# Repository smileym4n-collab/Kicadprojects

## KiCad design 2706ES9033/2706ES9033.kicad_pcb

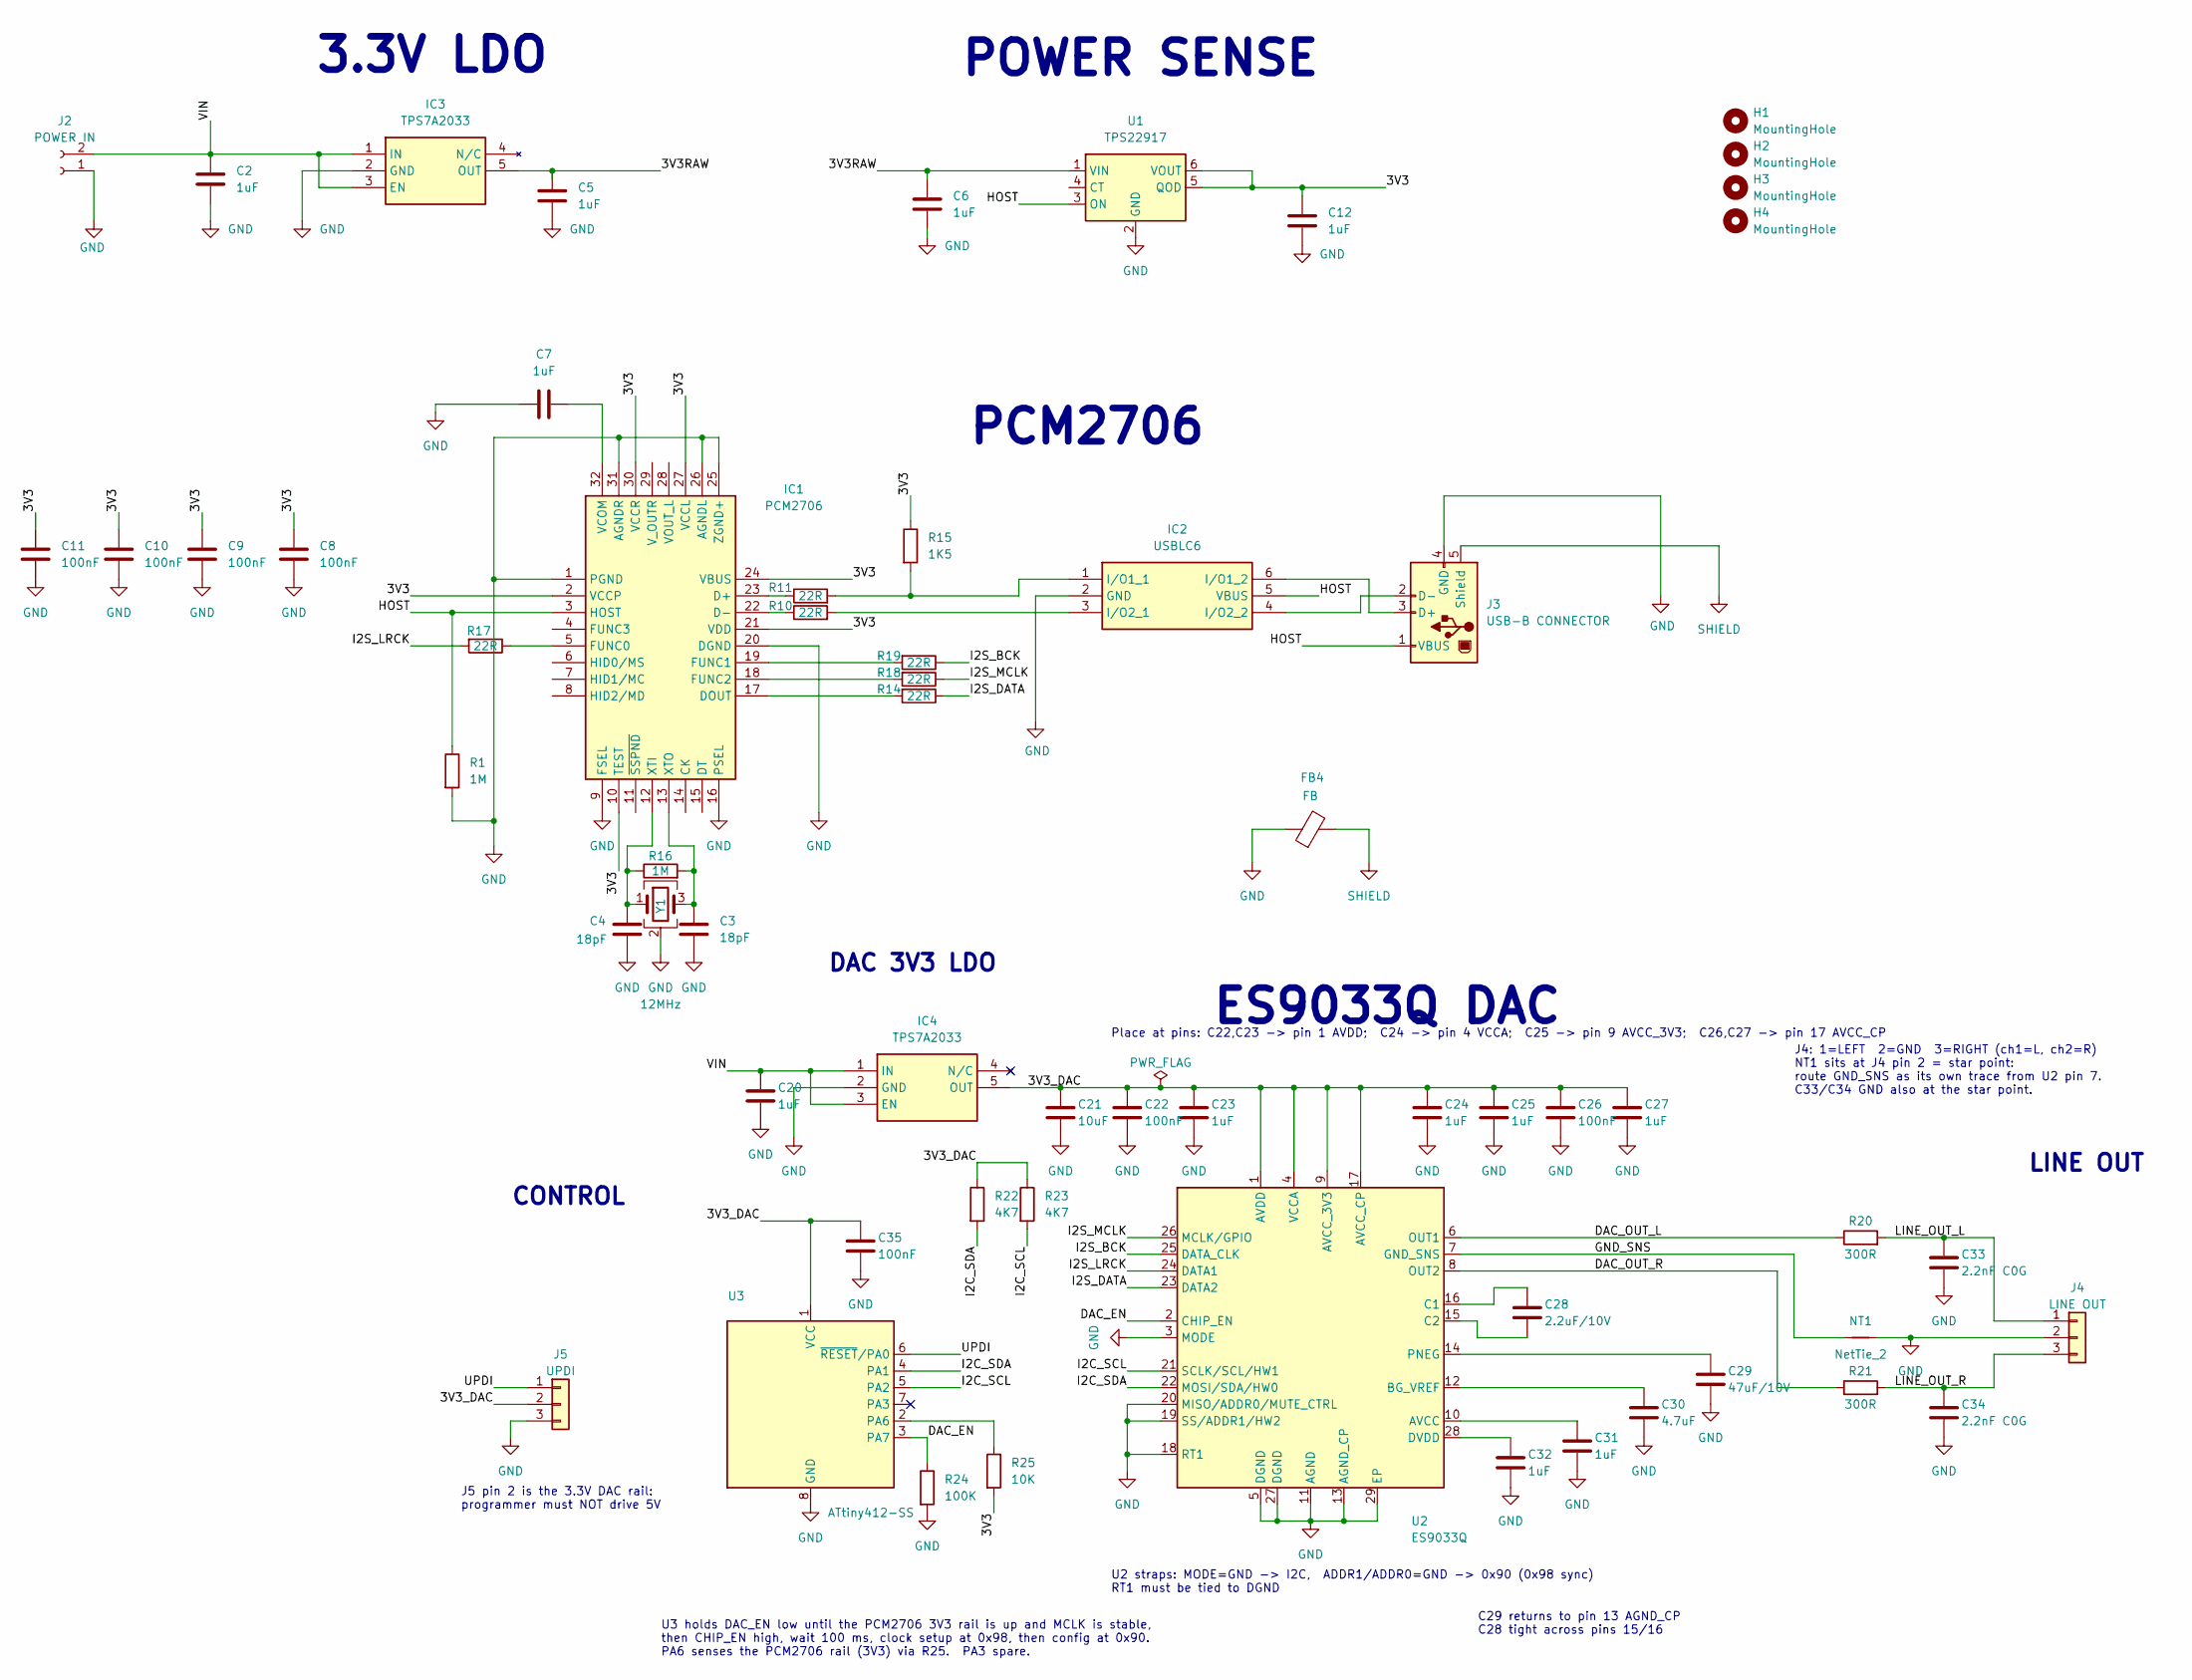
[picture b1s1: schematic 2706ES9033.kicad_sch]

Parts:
C2, C5, C6, C7, C12: 1uF; C_0805_2012Metric_Pad1.18x1.45mm_HandSolder
C3, C4: 18pF; C_0603_1608Metric_Pad1.08x0.95mm_HandSolder
C8, C9, C10, C11: 100nF; C_0603_1608Metric_Pad1.08x0.95mm_HandSolder
C20, C23, C24, C25, C27, C31, C32: 1uF; C_0805_2012Metric_Pad1.18x1.45mm_HandSolder; MPN C0805C105K3RACTU
C21: 10uF; C_1206_3216Metric_Pad1.33x1.80mm_HandSolder; MPN TMK316B7106KL-TD
C22, C26, C35: 100nF; C_0603_1608Metric_Pad1.08x0.95mm_HandSolder; MPN MC0603B104K500CT
C28: 2.2uF/10V; C_0805_2012Metric_Pad1.18x1.45mm_HandSolder; MPN CL21B225KPFNNNE
C29: 47uF/10V; C_1206_3216Metric_Pad1.33x1.80mm_HandSolder; MPN CL31A476MPHNNNE
C30: 4.7uF; C_0805_2012Metric_Pad1.18x1.45mm_HandSolder; MPN CL21A475KAQNNNE
C33, C34: 2.2nF C0G; C_0805_2012Metric_Pad1.18x1.45mm_HandSolder; MPN GCM2165C2A222FA16D
FB4: FB; L_1206_3216Metric_Pad1.42x1.75mm_HandSolder
H1, H2, H3, H4: MountingHole; MountingHole_3.2mm_M3
IC1: PCM2706; PCM2706C; Mouser Part Number 595-PCM2706CPJTR
IC2: USBLC6; SOT-23-6_Handsoldering; Mouser Part Number 511-USBLC6-2SC6
IC3: TPS7A2033; SOT95P280X145-5N; Mouser Part Number 595-TPS7A2033PDBVR
IC4: TPS7A2033; SOT95P280X145-5N; MPN TPS7A2033PDBVR
J2: POWER IN; JST_XH_B2B-XH-A_1x02_P2.50mm_Vertical
J3: USB-B CONNECTOR; USBC
J4: LINE OUT; Molex_KK-254_AE-6410-03A_1x03_P2.54mm_Vertical; MPN MC34631
J5: UPDI; Molex_KK-254_AE-6410-03A_1x03_P2.54mm_Vertical; MPN MC34631
NT1: NetTie_2; NetTie-2_SMD_Pad0.5mm
R1, R16: 1M; R_0603_1608Metric_Pad0.98x0.95mm_HandSolder
R10, R11, R14, R17, R18, R19: 22R; R_0603_1608Metric_Pad0.98x0.95mm_HandSolder
R15: 1K5; R_0603_1608Metric_Pad0.98x0.95mm_HandSolder
R20, R21: 300R; R_0805_2012Metric_Pad1.20x1.40mm_HandSolder; MPN ERA-6AEB301V
R22, R23: 4K7; R_0805_2012Metric_Pad1.20x1.40mm_HandSolder; MPN RMCF0805FT4K70
R24: 100K; R_0805_2012Metric_Pad1.20x1.40mm_HandSolder; MPN RK73B2ATTE104J
R25: 10K; R_0805_2012Metric_Pad1.20x1.40mm_HandSolder; MPN RK73B2ATTD103J
U1: TPS22917; SOT-23-6
U2: ES9033Q; ESS_QFN-28-1EP_5x5mm_P0.5mm_EP3.15x3.15mm; MPN ES9033Q
U3: ATtiny412-SS; SOIC-8_3.9x4.9mm_P1.27mm; MPN ATTINY412-SSN
Y1: 12MHz; Crystal_SMD_3225-4Pin_3.2x2.5mm; MPN 830108338809; Mouser Part Number 710-830108338809

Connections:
/3V3: C8.1, C9.1, C10.1, C11.1, C12.1, IC1.2 (VCCP), IC1.10 (TEST), IC1.21 (VDD), IC1.24 (VBUS), IC1.27 (VCCL), IC1.30 (VCCR), R15.1, R25.2, U1.5 (QOD), U1.6 (VOUT)
/3V3RAW: C5.1, C6.1, IC3.5 (OUT), U1.1 (VIN)
/3V3_DAC: C21.1, C22.1, C23.1, C24.1, C25.1, C26.1, C27.1, C35.1, IC4.5 (OUT), J5.2, R22.1, R23.1, U2.1 (AVDD), U2.4 (VCCA), U2.9 (AVCC_3V3), U2.17 (AVCC_CP), U3.1 (VCC)
/DAC_EN: R24.1, U2.2 (CHIP_EN), U3.3 (PA7)
/DAC_OUT_L: R20.1, U2.6 (OUT1)
/DAC_OUT_R: R21.1, U2.8 (OUT2)
/GND_SNS: NT1.1, U2.7 (GND_SNS)
/HOST: IC1.3 (HOST), IC2.5 (VBUS), J3.1 (VBUS), R1.1, U1.3 (ON)
/I2C_SCL: R23.2, U2.21 (SCLK/SCL/HW1), U3.5 (PA2)
/I2C_SDA: R22.2, U2.22 (MOSI/SDA/HW0), U3.4 (PA1)
/I2S_BCK: R19.1, U2.25 (DATA_CLK)
/I2S_DATA: R14.1, U2.23 (DATA2)
/I2S_LRCK: R17.2, U2.24 (DATA1)
/I2S_MCLK: R18.1, U2.26 (MCLK/GPIO)
/LINE_OUT_L: C33.1, J4.1, R20.2
/LINE_OUT_R: C34.1, J4.3, R21.2
/UPDI: J5.1, U3.6 (~RESET/PA0)
/VIN: C2.1, C20.1, IC3.1 (IN), IC3.3 (EN), IC4.1 (IN), IC4.3 (EN), J2.2
GND: C2.2, C3.2, C4.2, C5.2, C6.2, C7.1, C8.2, C9.2, C10.2, C11.2, C12.2, C20.2, C21.2, C22.2, C23.2, C24.2, C25.2, C26.2, C27.2, C29.2, C30.2, C31.2, C32.2, C33.2, C34.2, C35.2, FB4.1, IC1.1 (PGND), IC1.9 (FSEL), IC1.16 (PSEL), IC1.20 (DGND), IC1.25 (ZGND+), IC1.26 (AGNDL), IC1.31 (AGNDR), IC2.2 (GND), IC3.2 (GND), IC4.2 (GND), J2.1, J3.4 (GND), J4.2, J5.3, NT1.2, R1.2, R24.2, U1.2 (GND), U2.3 (MODE), U2.5 (DGND), U2.11 (AGND), U2.13 (AGND_CP), U2.18 (RT1), U2.19 (SS/ADDR1/HW2), U2.20 (MISO/ADDR0/MUTE_CTRL), U2.27 (DGND), U2.29 (EP), U3.8 (GND), Y1.2 (G), Y1.4 (G)
unnamed: IC1.23 (D+), R11.1
unnamed: IC1.22 (D-), R10.1
unnamed: IC1.17 (DOUT), R14.2
unnamed: IC1.5 (FUNC0), R17.1
unnamed: IC1.19 (FUNC1), R19.2
unnamed: IC1.18 (FUNC2), R18.2
unnamed: C7.2, IC1.32 (VCOM)
unnamed: C4.1, IC1.12 (XTI), R16.1, Y1.1
unnamed: C3.1, IC1.13 (XTO), R16.2, Y1.3
unnamed: IC2.1 (I/O1_1), R11.2, R15.2
unnamed: IC2.6 (I/O1_2), J3.3 (D+)
unnamed: IC2.3 (I/O2_1), R10.2
unnamed: IC2.4 (I/O2_2), J3.2 (D-)
unnamed: C31.1, U2.10 (AVCC)
unnamed: C30.1, U2.12 (BG_VREF)
unnamed: C28.1, U2.16 (C1)
unnamed: C28.2, U2.15 (C2)
unnamed: C32.1, U2.28 (DVDD)
unnamed: C29.1, U2.14 (PNEG)
unnamed: R25.1, U3.2 (PA6)
SHIELD: FB4.2, J3.5 (Shield)

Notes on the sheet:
3.3V LDO
ES9033Q DAC
U3 holds DAC_EN low until the PCM2706 3V3 rail is up and MCLK is stable, then CHIP_EN high, wait 100 ms, clock setup at 0x98, then config at 0x90. PA6 senses the PCM2706 rail (3V3) via R25. PA3 spare.
J4: 1=LEFT 2=GND 3=RIGHT (ch1=L, ch2=R) NT1 sits at J4 pin 2 = star point: route GND_SNS as its own trace from U2 pin 7. C33/C34 GND also at the star point.
U2 straps: MODE=GND -> I2C, ADDR1/ADDR0=GND -> 0x90 (0x98 sync) RT1 must be tied to DGND
PCM2706
CONTROL
POWER SENSE
Place at pins: C22,C23 -> pin 1 AVDD; C24 -> pin 4 VCCA; C25 -> pin 9 AVCC_3V3; C26,C27 -> pin 17 AVCC_CP
LINE OUT
C29 returns to pin 13 AGND_CP C28 tight across pins 15/16
J5 pin 2 is the 3.3V DAC rail: programmer must NOT drive 5V
DAC 3V3 LDO

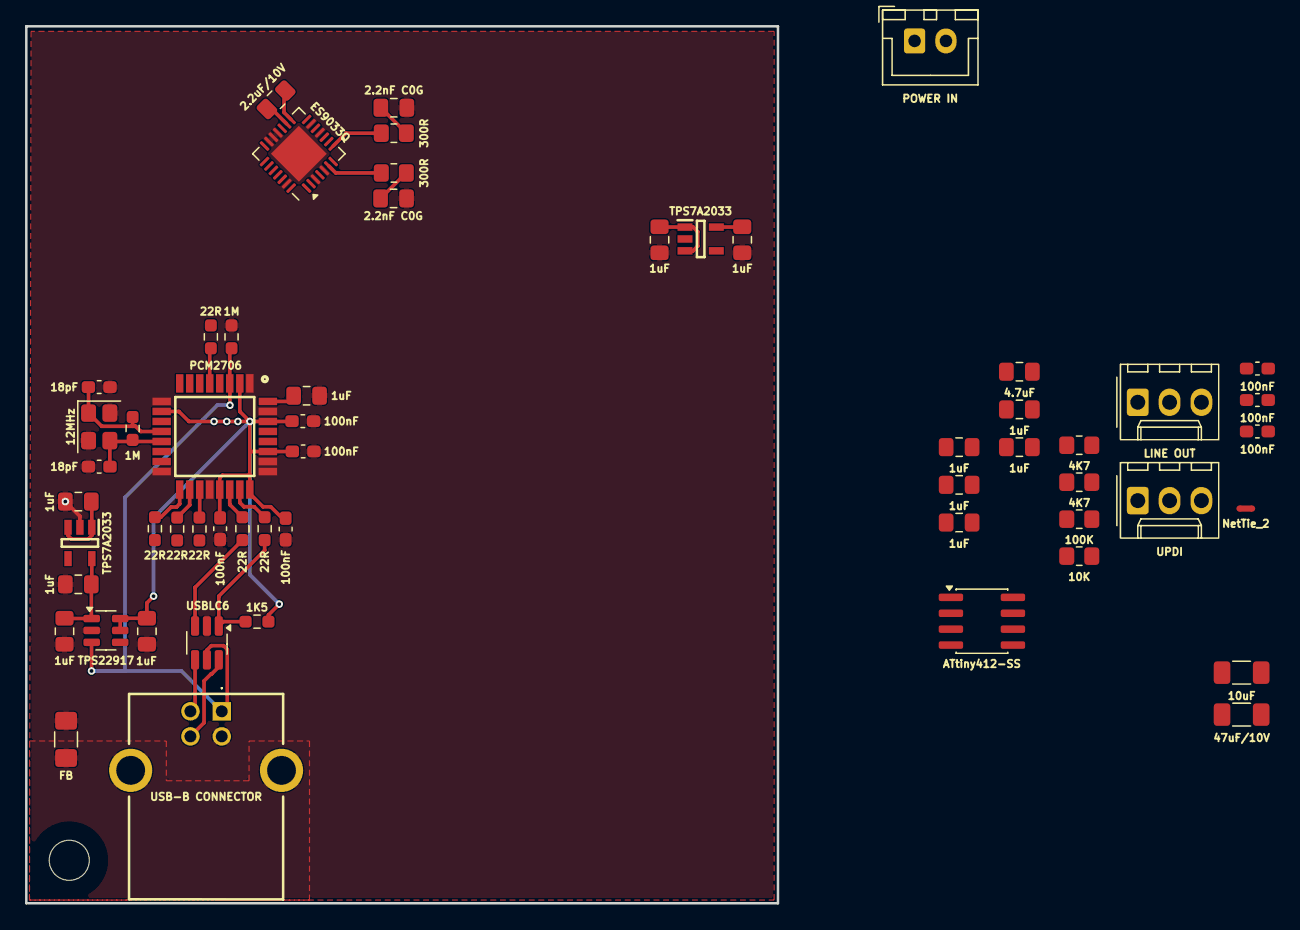
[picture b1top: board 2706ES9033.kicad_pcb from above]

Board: 2 copper layers, 60.0 x 70.0 mm, 60 parts (0 on the bottom side), 40 nets.

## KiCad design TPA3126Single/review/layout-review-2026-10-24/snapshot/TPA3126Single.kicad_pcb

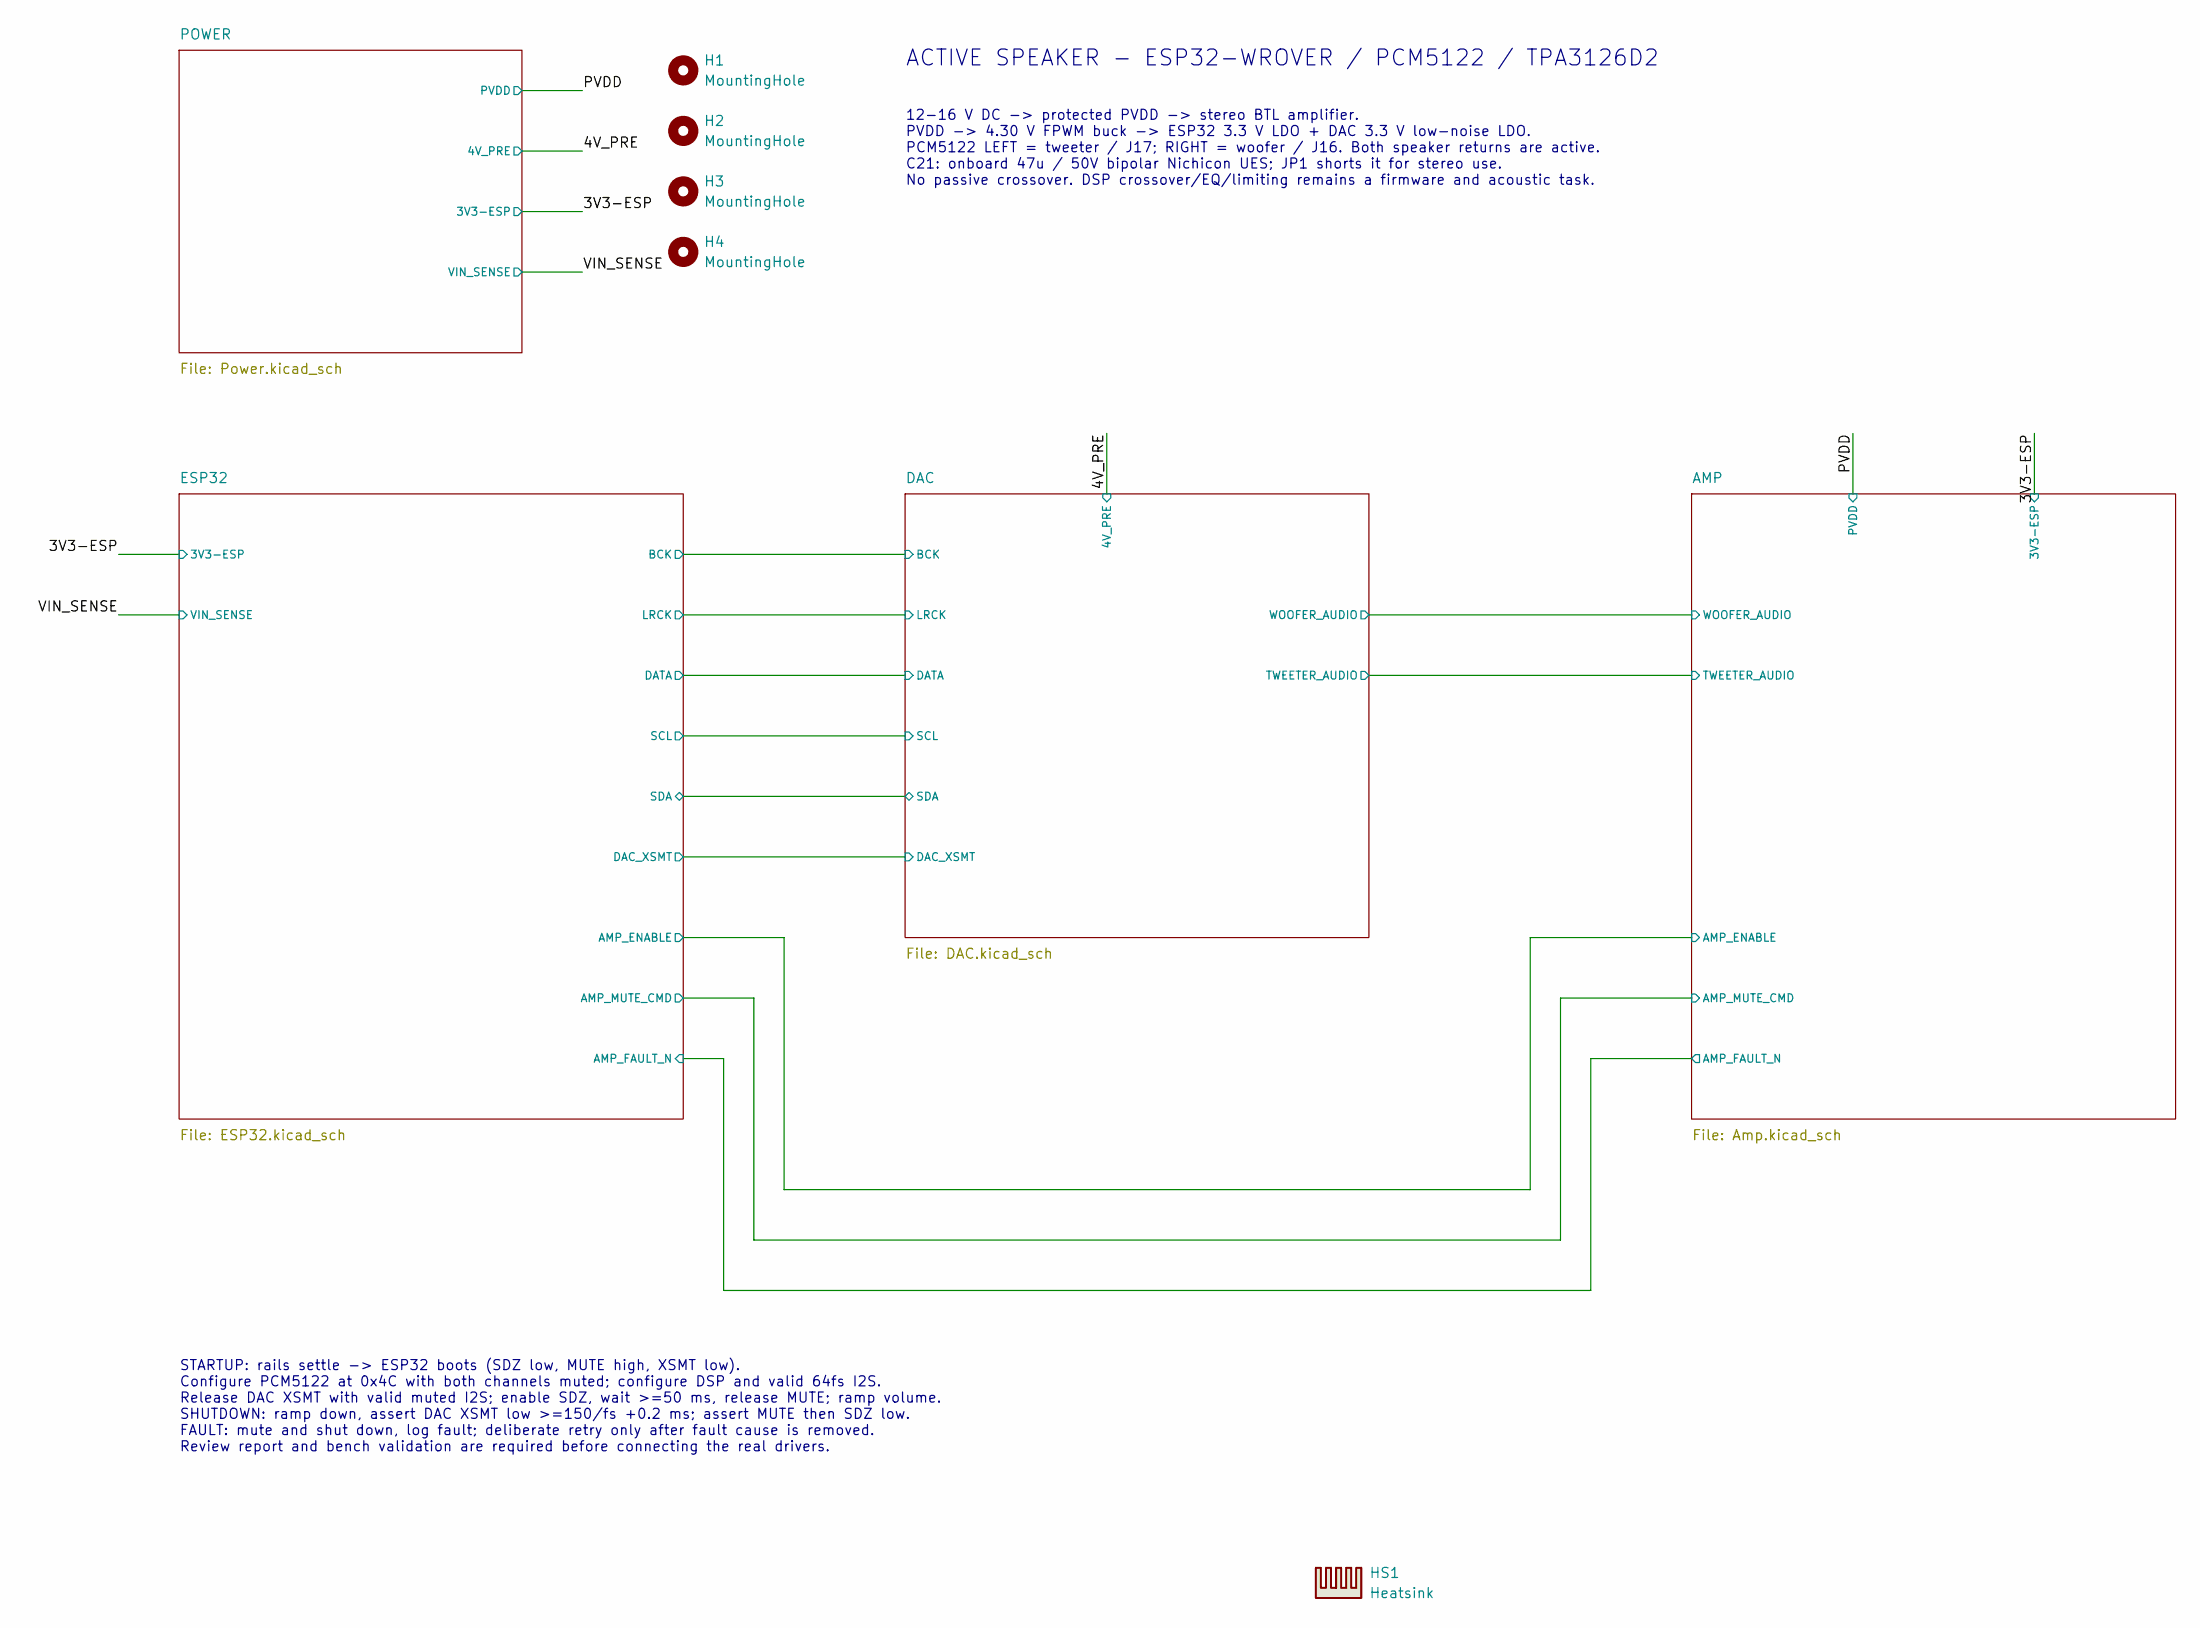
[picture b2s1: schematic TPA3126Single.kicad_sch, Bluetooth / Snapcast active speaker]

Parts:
H1, H2, H3, H4: MountingHole; MountingHole_3.2mm_M3
HS1: Heatsink; Heatsink_ATS_ATS-TI1OP-521-C1-R1_50x13.9mm_H25mm_P40mm; MPN ATS-TI1OP-521-C1-R1

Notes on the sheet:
STARTUP: rails settle -> ESP32 boots (SDZ low, MUTE high, XSMT low). Configure PCM5122 at 0x4C with both channels muted; configure DSP and valid 64fs I2S. Release DAC XSMT with valid muted I2S; enable SDZ, wait >=50 ms, release MUTE; ramp volume. SHUTDOWN: ramp down, assert DAC XSMT low >=150/fs +0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
ACTIVE SPEAKER - ESP32-WROVER / PCM5122 / TPA3126D2
12-16 V DC -> protected PVDD -> stereo BTL amplifier. PVDD -> 4.30 V FPWM buck -> ESP32 3.3 V LDO + DAC 3.3 V low-noise LDO. PCM5122 LEFT = tweeter / J17; RIGHT = woofer / J16. Both speaker returns are active. C21: onboard 47u / 50V bipolar Nichicon UES; JP1 shorts it for stereo use. No passive cro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

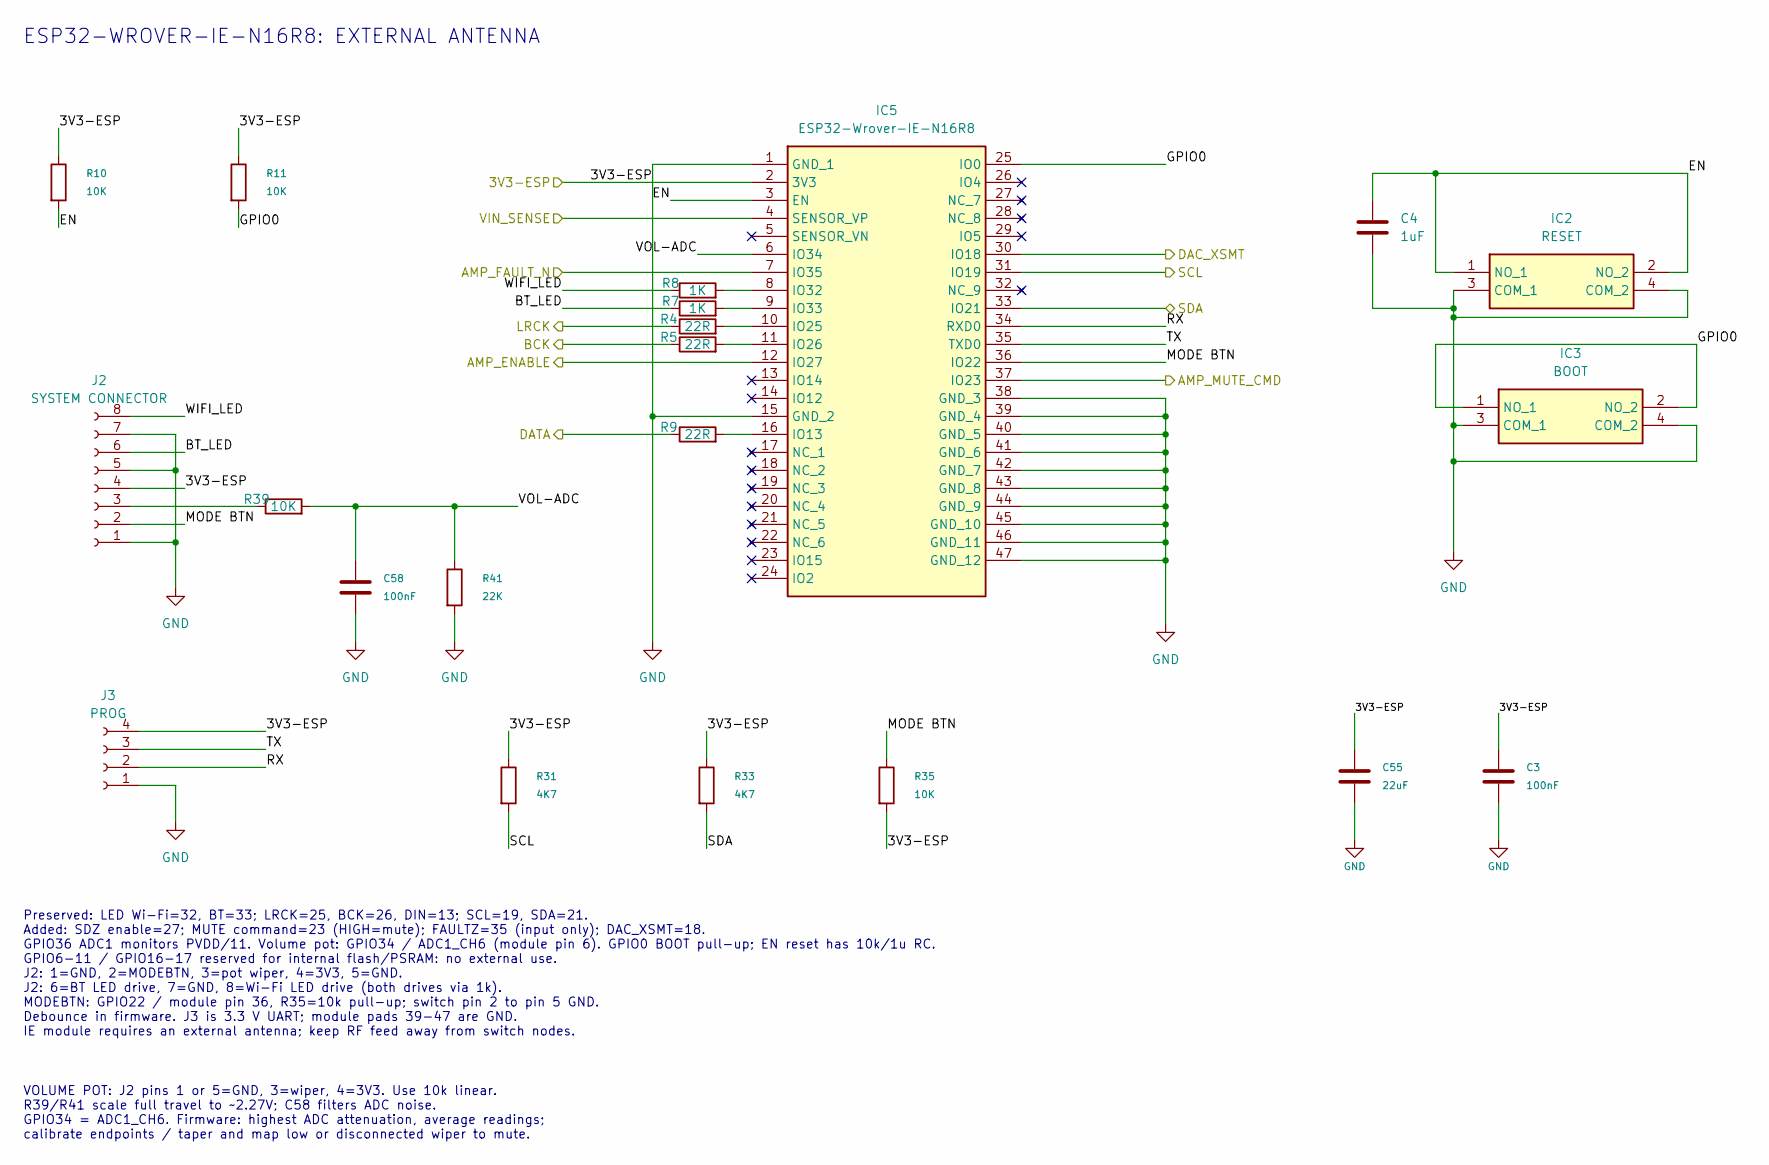
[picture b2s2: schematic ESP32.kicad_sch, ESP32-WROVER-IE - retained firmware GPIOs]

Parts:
C3, C58: 100nF; C_1206_3216Metric_Pad1.33x1.80mm_HandSolder; MPN C1206C104K5RACTU
C4: 1uF; C_1206_3216Metric_Pad1.33x1.80mm_HandSolder; MPN CL31B105KBHNFNE
C55: 22uF; C_1206_3216Metric_Pad1.33x1.80mm_HandSolder; MPN CL31A226KAHNNNE
IC2: RESET; TS026650BK100SCRD; Mouser Part Number 179-TS026650BK100SCR
IC3: BOOT; TS026650BK100SCRD; Mouser Part Number 179-TS026650BK100SCR
IC5: ESP32-Wrover-IE-N16R8; ESP32-WROVER-IE-N16R8; Mouser Part Number 356-ESP32WRVIE2864UC
J2: SYSTEM CONNECTOR; JST_XH_B8B-XH-A_1x08_P2.50mm_Vertical; MPN B8B-XH-A(LF)(SN)
J3: PROG; PinHeader_1x04_P2.54mm_Vertical
R4, R5, R9: 22R; R_0603_1608Metric_Pad0.98x0.95mm_HandSolder; MPN RK73B1JTTD220J
R7, R8: 1K; R_0805_2012Metric_Pad1.20x1.40mm_HandSolder
R10, R11, R35: 10K; R_0603_1608Metric_Pad0.98x0.95mm_HandSolder
R31, R33: 4K7; R_0805_2012Metric_Pad1.20x1.40mm_HandSolder; MPN RMCF0805FT4K70
R39: 10K; R_0805_2012Metric_Pad1.20x1.40mm_HandSolder; MPN RK73B2ATTD103J
R41: 22K; R_0805_2012Metric_Pad1.20x1.40mm_HandSolder; MPN RR1220P-223-D

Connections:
/3V3-ESP: C3.1, C55.1, IC5.2 (3V3), J2.4, J3.4, R10.1, R11.1, R31.1, R33.1, R35.2; also elsewhere on the board
/AMP/AMP_ENABLE: IC5.12 (IO27); also elsewhere on the board
/AMP/AMP_FAULT_N: IC5.7 (IO35); also elsewhere on the board
/AMP/AMP_MUTE_CMD: IC5.37 (IO23); also elsewhere on the board
/DAC/BCK: R5.1; also elsewhere on the board
/DAC/DAC_XSMT: IC5.30 (IO18); also elsewhere on the board
/DAC/DATA: R9.1; also elsewhere on the board
/DAC/LRCK: R4.1; also elsewhere on the board
/ESP32/BT_LED: J2.6, R7.1
/ESP32/EN: C4.1, IC2.1 (NO_1), IC2.2 (NO_2), IC5.3 (EN), R10.2
/ESP32/GPIO0: IC3.1 (NO_1), IC3.2 (NO_2), IC5.25 (IO0), R11.2
/ESP32/MODE BTN: IC5.36 (IO22), J2.2, R35.1
/ESP32/RX: IC5.34 (RXD0), J3.2
/ESP32/SCL: IC5.31 (IO19), R31.2; also elsewhere on the board
/ESP32/SDA: IC5.33 (IO21), R33.2; also elsewhere on the board
/ESP32/TX: IC5.35 (TXD0), J3.3
/ESP32/VOL-ADC: C58.1, IC5.6 (IO34), R39.2, R41.1
/ESP32/WIFI_LED: J2.8, R8.1
/VIN_SENSE: IC5.4 (SENSOR_VP); also elsewhere on the board
GND: C3.2, C4.2, C55.2, C58.2, IC2.3 (COM_1), IC2.4 (COM_2), IC3.3 (COM_1), IC3.4 (COM_2), IC5.1 (GND_1), IC5.15 (GND_2), IC5.38 (GND_3), IC5.39 (GND_4), IC5.40 (GND_5), IC5.41 (GND_6), IC5.42 (GND_7), IC5.43 (GND_8), IC5.44 (GND_9), IC5.45 (GND_10), IC5.46 (GND_11), IC5.47 (GND_12), J2.1, J2.5, J2.7, J3.1, R41.2; also elsewhere on the board
unnamed: IC5.16 (IO13), R9.2
unnamed: IC5.10 (IO25), R4.2
unnamed: IC5.11 (IO26), R5.2
unnamed: IC5.8 (IO32), R8.2
unnamed: IC5.9 (IO33), R7.2
unnamed: J2.3, R39.1

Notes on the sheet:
ESP32-WROVER-IE-N16R8: EXTERNAL ANTENNA
VOLUME POT: J2 pins 1 or 5=GND, 3=wiper, 4=3V3. Use 10k linear. R39/R41 scale full travel to ~2.27V; C58 filters ADC noise. GPIO34 = ADC1_CH6. Firmware: highest ADC attenuation, average readings; calibrate endpoints / taper and map low or disconnected wiper to mute.
Preserved: LED Wi-Fi=32, BT=33; LRCK=25, BCK=26, DIN=13; SCL=19, SDA=21. Added: SDZ enable=27; MUTE command=23 (HIGH=mute); FAULTZ=35 (input only); DAC_XSMT=18. GPIO36 ADC1 monitors PVDD/11. Volume pot: GPIO34 / ADC1_CH6 (module pin 6). GPIO0 BOOT pull-up; EN reset has 10k/1u RC. GPIO6-11 / GPIO16-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

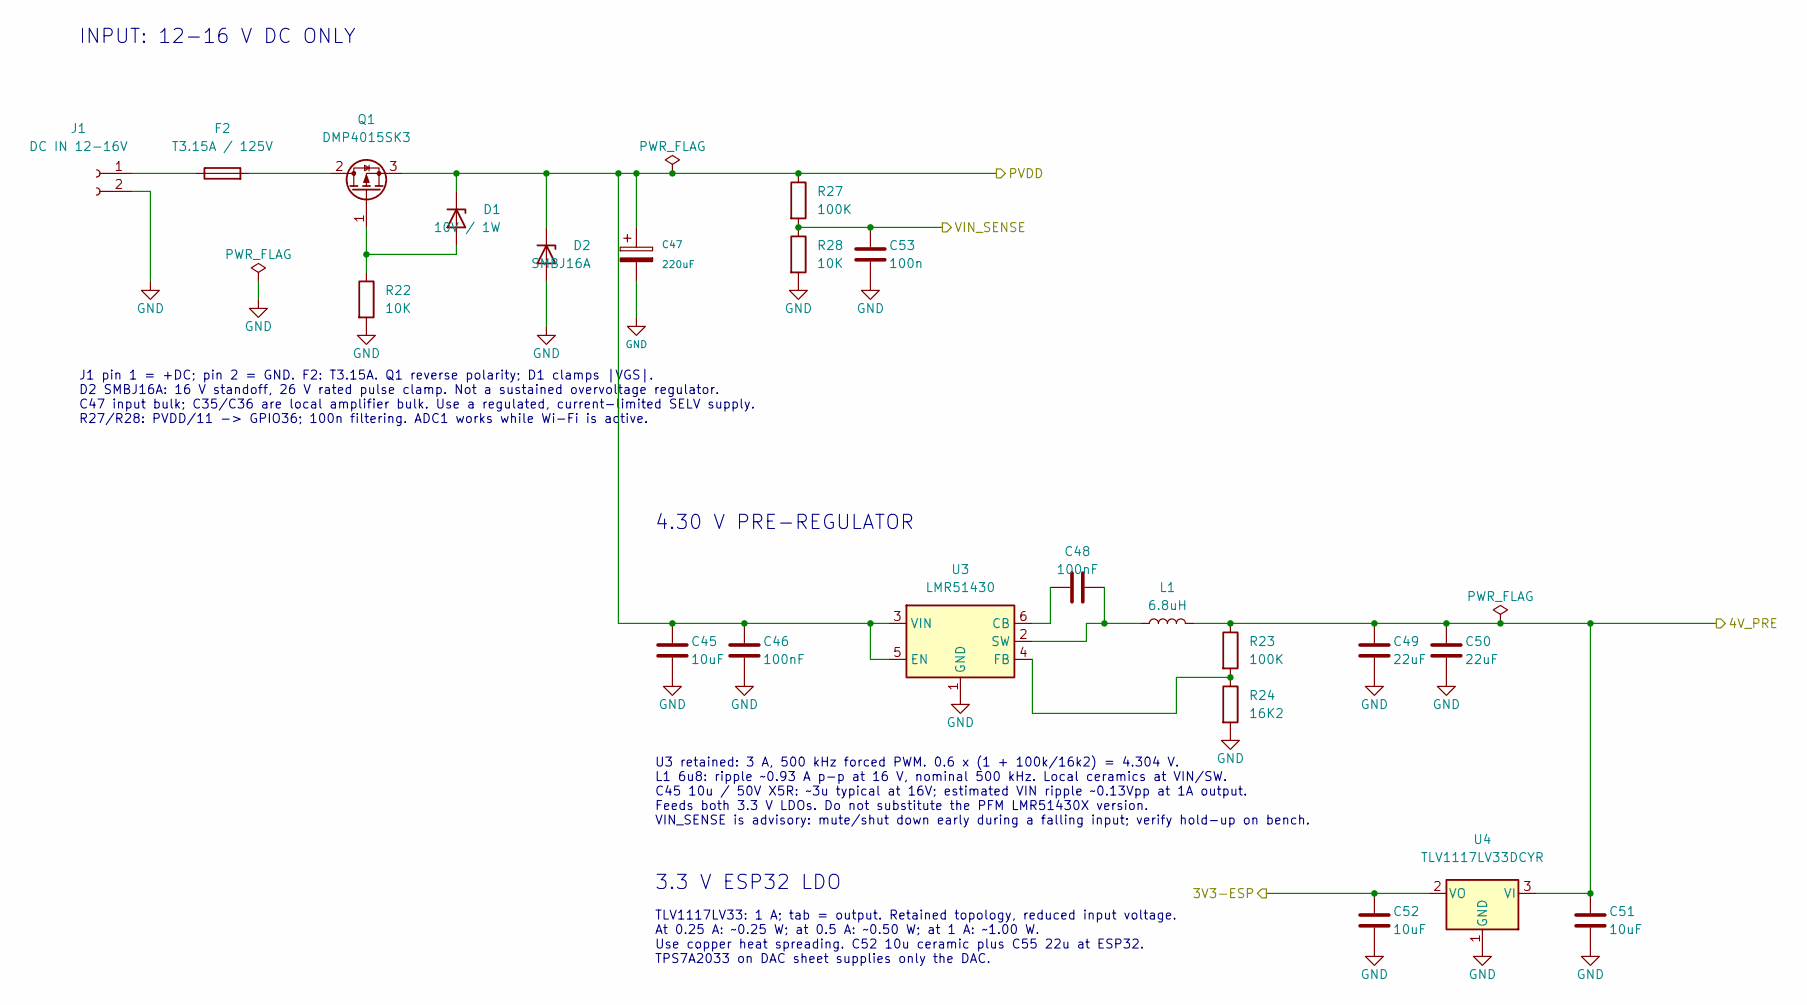
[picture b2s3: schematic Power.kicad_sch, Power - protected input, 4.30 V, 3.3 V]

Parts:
C45: 10uF; C_1206_3216Metric_Pad1.33x1.80mm_HandSolder; Voltage_Rating 50 V; Tolerance 10%; Manufacturer_Part_Number CL31A106KBHNNNE
C46, C48: 100nF; C_0603_1608Metric_Pad1.08x0.95mm_HandSolder; Manufacturer_Part_Number MC0603B104K500CT
C47: 220uF; CP_Radial_D8.0mm_P3.50mm; MPN 35ZLH220MEFC8X11.5
C49, C50: 22uF; C_1206_3216Metric_Pad1.33x1.80mm_HandSolder; Manufacturer_Part_Number CL31A226KAHNNNE
C51, C52: 10uF; C_0805_2012Metric_Pad1.18x1.45mm_HandSolder; Manufacturer_Part_Number CL21A106KOQNNNF
C53: 100n; C_0603_1608Metric_Pad1.08x0.95mm_HandSolder; Manufacturer_Part_Number MC0603B104K500CT
D1: 10V / 1W; D_DO-41_SOD81_P10.16mm_Horizontal; Manufacturer_Part_Number 1N4740ATR
D2: SMBJ16A; D_SMB; Manufacturer_Part_Number SMBJ16A
F2: T3.15A / 125V; Fuse_Littelfuse_395Series; MPN 39613150000
J1: DC IN 12-16V; Molex_KK-396_5273-02A_1x02_P3.96mm_Vertical; Manufacturer_Part_Number 09-65-2028
L1: 6.8uH; SRP6030WA-6R8M; Manufacturer_Part_Number SRP6030WA-6R8M
Q1: DMP4015SK3; TO-252-2; Manufacturer_Part_Number DMP4015SK3-13
R22, R28: 10K; R_0603_1608Metric_Pad0.98x0.95mm_HandSolder; Manufacturer_Part_Number RC0603FR-0710KL
R23, R27: 100K; R_0603_1608Metric_Pad0.98x0.95mm_HandSolder; Manufacturer_Part_Number RC0603FR-07100KL
R24: 16K2; R_0603_1608Metric_Pad0.98x0.95mm_HandSolder; Manufacturer_Part_Number RC0603FR-0716K2L
U3: LMR51430; TSOT-23-6; Manufacturer_Part_Number LMR51430XFDDCR
U4: TLV1117LV33DCYR; SOT-223-3_TabPin2; Manufacturer_Part_Number TLV1117LV33DCYR

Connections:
/3V3-ESP: C52.1, U4.2 (VO); also elsewhere on the board
/4V_PRE: C49.1, C50.1, C51.1, L1.2, R23.1, U4.3 (VI); also elsewhere on the board
/PVDD: C45.1, C46.1, C47.1, D1.1 (K), D2.1 (K), Q1.3 (S), R27.1, U3.3 (VIN), U3.5 (EN); also elsewhere on the board
/VIN_SENSE: C53.1, R27.2, R28.1; also elsewhere on the board
GND: C45.2, C46.2, C47.2, C49.2, C50.2, C51.2, C52.2, C53.2, D2.2 (A), J1.2, R22.2, R24.2, R28.2, U3.1 (GND), U4.1 (GND); also elsewhere on the board
unnamed: D1.2 (A), Q1.1 (G), R22.1
unnamed: F2.1, J1.1
unnamed: F2.2, Q1.2 (D)
unnamed: C48.1, U3.6 (CB)
unnamed: R23.2, R24.1, U3.4 (FB)
unnamed: C48.2, L1.1, U3.2 (SW)

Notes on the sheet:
4.30 V PRE-REGULATOR
3.3 V ESP32 LDO
INPUT: 12-16 V DC ONLY
U3 retained: 3 A, 500 kHz forced PWM. 0.6 x (1 + 100k/16k2) = 4.304 V. L1 6u8: ripple ~0.93 A p-p at 16 V, nominal 500 kHz. Local ceramics at VIN/SW. C45 10u / 50V X5R: ~3u typical at 16V; estimated VIN ripple ~0.13Vpp at 1A output. Feeds both 3.3 V LDOs. Do not substitute the PFM LMR51430X version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
TLV1117LV33: 1 A; tab = output. Retained topology, reduced input voltage. At 0.25 A: ~0.25 W; at 0.5 A: ~0.50 W; at 1 A: ~1.00 W. Use copper heat spreading. C52 10u ceramic plus C55 22u at ESP32. TPS7A2033 on DAC sheet supplies only the DAC.
J1 pin 1 = +DC; pin 2 = GND. F2: T3.15A. Q1 reverse polarity; D1 clamps |VGS|. D2 SMBJ16A: 16 V standoff, 26 V rated pulse clamp. Not a sustained overvoltage regulator. C47 input bulk; C35/C36 are local amplifier bulk. Use a regulated, current-limited SELV supply. R27/R28: PVDD/11 -> GPIO36; 100n f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

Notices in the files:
PreAmpPico/PreAmpPico.kicad_pcb:
© Tom Watson Audio 2026
